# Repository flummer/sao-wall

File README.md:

# SAO Wall

This is a design for a large PCB (300x400mm) with 16 SAO connectors to work either as a standalone display (fits in an IKEA RÖDALM picture frame) or be monted along with other panels to form a larger wall for displaying many SAOs.

This is heavily inspired by [Brian Benchoffs SAO Wall](https://bbenchoff.github.io/pages/ShittyWall.html), that has been used at several Supercon events, but this design does a few things slightly different, not least the power setup.

## Main concept and idea

The design is separated into two parts:

- SAO Connector board, which is the large PCB, that has all the connectors, polyfuses for each output and then a set of connectors for hooking up to the 4 power rails, the 2 I2C busses and all the GPIO pins for all SAOs
- USB-C PD and Pico controll board is the smaller board that has the voltage regulators (4x AP63203WU-7 buck converters), USB-C PD controller (STUSB4531) and a footprint for a Raspberry Pi Pico (1 or 2).

The setup with two boards is done so that the more generic part (the connector PCB) that is also a bit on the expensive side can be ordered once and maybe a combined order for multiple people, and then the more opinionated element with the powering circuit and maybe a micro controller can be easier made in low volume (most simple is a piece of proto board and a simple 3.3v poser supply).

The USB-C PD power setup that is included here is meant to work nicely with most USB-C power supplies and at the same time be able to power all 16 SAOs to the full specification of the SAO standard (250mA @ 3.3V for each SAO).

The Raspberry Pi Pico is connected very similar to hos the [Hackaday SAO Badge](https://github.com/Hack-a-Day/2024-Supercon-8-Add-On-Badge) was made, with 2 I2C busses (using the same pins) and hooked up to GPIO pins of most of the SAOs (10 out of the 16) as there is a limited number of available connections on the Pico. It's not 100% pin compatible with the Hackaday SAO Badge, but it should be an easy tweak if you would like to run the same firmware.

## Designed in KiCad v10

To open the project, you will need to install the most recent release (v10), KiCad v9 or earlier won't open this design directly.

[Electronics schematics for the connector board as a PDF file](https://github.com/flummer/sao-wall/blob/main/sao-connector-board-schematics.pdf) and [Electronics schematics for the USB-C PD and Pico control board as a PDF file](https://github.com/flummer/sao-wall/blob/main/usb-pd-pico-controller-schematics.pdf) are included for reference.

## License

The hardware design of the `main` branch of this repository is released under the following license:

* the "Creative Commons Attribution-ShareAlike 4.0 International License"
  (CC BY-SA 4.0) full text of this license is included in the LICENSE file
  and a copy can also be found at
  [http://creativecommons.org/licenses/by-sa/4.0/](http://creativecommons.org/licenses/by-sa/4.0/)

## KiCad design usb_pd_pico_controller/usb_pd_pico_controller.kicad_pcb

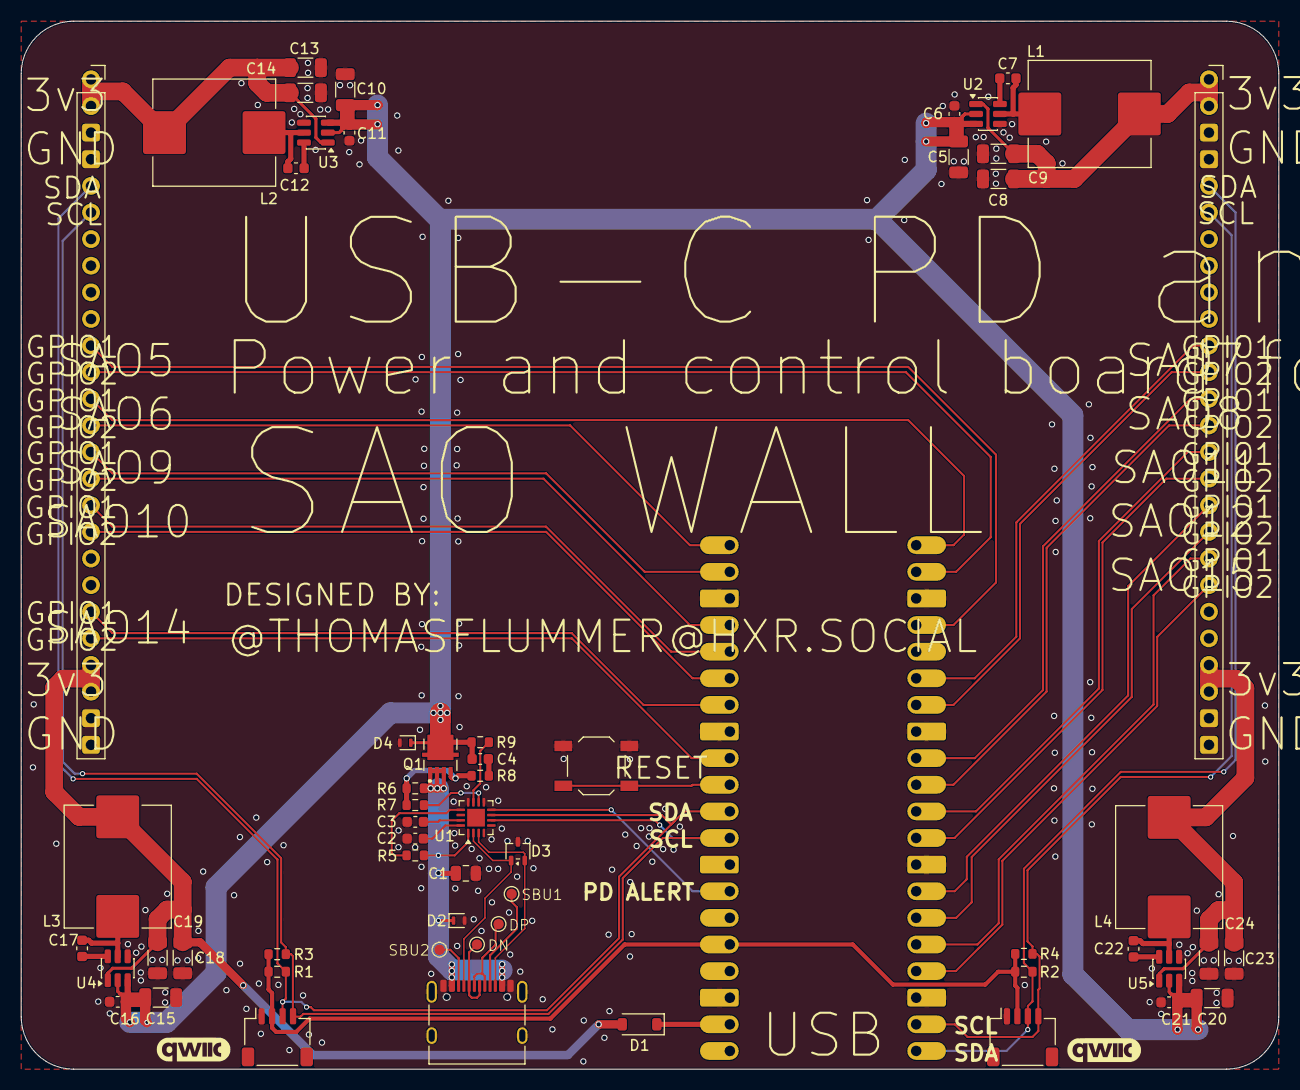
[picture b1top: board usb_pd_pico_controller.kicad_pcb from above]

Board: 2 copper layers, 120.0 x 100.0 mm, 59 parts (0 on the bottom side), 56 nets.

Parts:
C1: 4.7uF, 35V; C_0805_2012Metric
C2, C3: 1uF; C_0603_1608Metric
C4, C6, C7, C11, C12, C16, C17, C21, C22: 100nF, X5R/X7R, 50V; C_0603_1608Metric
C5, C10, C15, C20: 10uF, X5R/X7R, 35V; C_1206_3216Metric
C8, C9, C13, C14, C18, C19, C23, C24: 22uF, X5R/X7R, 25V; C_1206_3216Metric
D1: MBR120VLSFT1G; D_SOD-123
D2, D4: ESDA25P35-1U1M; ST_QFN-2L_1.6x1.0mm
D3: ESDA25W; SOT-323_SC-70
J1, J2: LCSC C145956; JST_SH_SM04B-SRSS-TB_1x04-1MP_P1.00mm_Horizontal
J3, J4: Conn_01x26_Socket; PinSocket_1x26_P2.54mm_Vertical
J5: USB_C_Receptacle_USB2.0_16P; USB_C_Receptacle_XKB_U262-16XN-4BVC11
J6, J7: Conn_01x20_Socket; PinSocket_1x20_P2.54mm_Vertical
L1, L2, L3, L4: 6.8uH; L_Sunlord_MWSA1005S
Q1: STL6P3LLH6; TRANS_STL6P3LLH6
R1, R2, R3, R4: 10K; R_0603_1608Metric
R5, R9: 1K; R_0603_1608Metric
R6: 100K; R_0603_1608Metric
R7: 22K; R_0603_1608Metric
R8: 100; R_0603_1608Metric
SW1: TS5220A; SW_SPST_TL3342
TP1, TP2, TP3, TP4: TestPoint; TestPoint_Pad_D1.0mm
U1: STUSB4531QTR; QFN-16-1EP_3x3mm_P0.5mm_EP1.7x1.7mm
U2, U3, U4, U5: AP63203WU; TSOT-23-6

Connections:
/PD Controller/CC1: D3.1 (K), J5.A5 (CC1), U1.2 (CC1)
/PD Controller/CC2: D3.2 (K), J5.B5 (CC2), U1.3 (CC2)
/PD Controller/D_N: J5.A7 (D-), J5.B7 (D-), TP2.1 (1_1)
/PD Controller/D_P: J5.A6 (D+), J5.B6 (D+), TP1.1 (1_1)
/PD Controller/SBU1: J5.A8 (SBU1), TP4.1 (1_1)
/PD Controller/SBU2: J5.B8 (SBU2), TP3.1 (1_1)
/PD Controller/VBUS: C1.1, D2.1 (K), J5.A4 (VBUS), J5.A9 (VBUS), J5.B4 (VBUS), J5.B9 (VBUS), Q1.1 (S1), Q1.2 (S1), Q1.3 (S1), R5.1, R6.1, U1.1 (VDD)
/RPi Pico X/RUN: J7.10, SW1.2 (B)
/RPi Pico X/VSYS: D1.1 (K), J7.19
/V_NEGOTIATED: C4.2, C5.1, C6.1, C10.1, C11.1, C15.1, C16.1, C20.1, C21.1, D4.1 (K), Q1.5_8 (D1), R9.1, U2.2 (EN), U2.3 (IN), U3.2 (EN), U3.3 (IN), U4.2 (EN), U4.3 (IN), U5.2 (EN), U5.3 (IN)
GND: C1.2, C2.2, C3.2, C5.2, C6.2, C8.2, C9.2, C10.2, C11.2, C13.2, C14.2, C15.2, C16.2, C18.2, C19.2, C20.2, C21.2, C23.2, C24.2, D2.2 (A), D3.3 (A), D4.2 (A), J1.1, J2.1, J3.3, J3.4, J3.25, J3.26, J4.3, J4.4, J4.25, J4.26, J5.A1 (GND), J5.A12 (GND), J5.B1 (GND), J5.B12 (GND), J5.SH (SHIELD), J6.3, J6.8, J6.13, J6.18, J7.3, J7.8, J7.18, SW1.1 (A), U1.9 (ADDR0), U1.12 (GND), U2.4 (GND), U3.4 (GND), U4.4 (GND), U5.4 (GND)
unnamed: C4.1, R8.1
unnamed: Q1.4 (G1), R6.2, R7.1, R8.2
unnamed: R9.2, U1.11 (DISCH)
unnamed: R7.2, U1.10 (VBUS_EN_SNK)
unnamed: R5.2, U1.13 (VBUS_VS_DISCH)
unnamed: C3.1, U1.15 (VREG_1V2)
unnamed: C2.1, U1.16 (VREG_2V7)
unnamed: C7.2, U2.6 (BST)
unnamed: C7.1, L1.1, U2.5 (SW)
unnamed: C12.2, U3.6 (BST)
unnamed: C12.1, L2.1, U3.5 (SW)
unnamed: C17.2, U4.6 (BST)
unnamed: C17.1, L3.1, U4.5 (SW)
unnamed: C22.2, U5.6 (BST)
unnamed: C22.1, L4.1, U5.5 (SW)
PD_ALERT: J7.14, U1.8 (ALERT)
SAO5_GPIO1: J3.11, J6.17
SAO5_GPIO2: J3.12, J6.19
SAO6_GPIO1: J3.13, J6.20
SAO6_GPIO2: J3.14, J7.1
SAO7_GPIO1: J4.11, J6.15
SAO7_GPIO2: J4.12, J6.14
SAO8_GPIO1: J4.13, J6.12
SAO8_GPIO2: J4.14, J6.11
SAO9_GPIO1: J3.15, J7.2
SAO9_GPIO2: J3.16, J7.4
SAO10_GPIO1: J3.17, J7.5
SAO10_GPIO2: J3.18, J7.6
SAO11_GPIO1: J4.15, J6.10
SAO11_GPIO2: J4.16, J6.9
SAO12_GPIO1: J4.17, J6.7
SAO12_GPIO2: J4.18, J6.6
SAO14_GPIO1: J3.21, J7.7
SAO14_GPIO2: J3.22, J7.9
SAO15_GPIO1: J4.19, J6.5
SAO15_GPIO2: J4.20, J6.4
SCL_LEFT: J1.4, J3.6, J7.12, R3.2, U1.6 (SCL)
SCL_RIGHT: J2.4, J4.6, J6.2, R4.2
SDA_LEFT: J1.3, J3.5, J7.11, R1.2, U1.7 (SDA)
SDA_RIGHT: J2.3, J4.5, J6.1, R2.2
VCC_PICO: J1.2, J2.2, J7.16, R1.1, R2.1, R3.1, R4.1
VCC_Q1: C8.1, C9.1, J4.1, J4.2, L1.2, U2.1 (FB)
VCC_Q2: C13.1, C14.1, J3.1, J3.2, L2.2, U3.1 (FB)
VCC_Q3: C18.1, C19.1, D1.2 (A), J3.23, J3.24, L3.2, U4.1 (FB)
VCC_Q4: C23.1, C24.1, J4.23, J4.24, L4.2, U5.1 (FB)

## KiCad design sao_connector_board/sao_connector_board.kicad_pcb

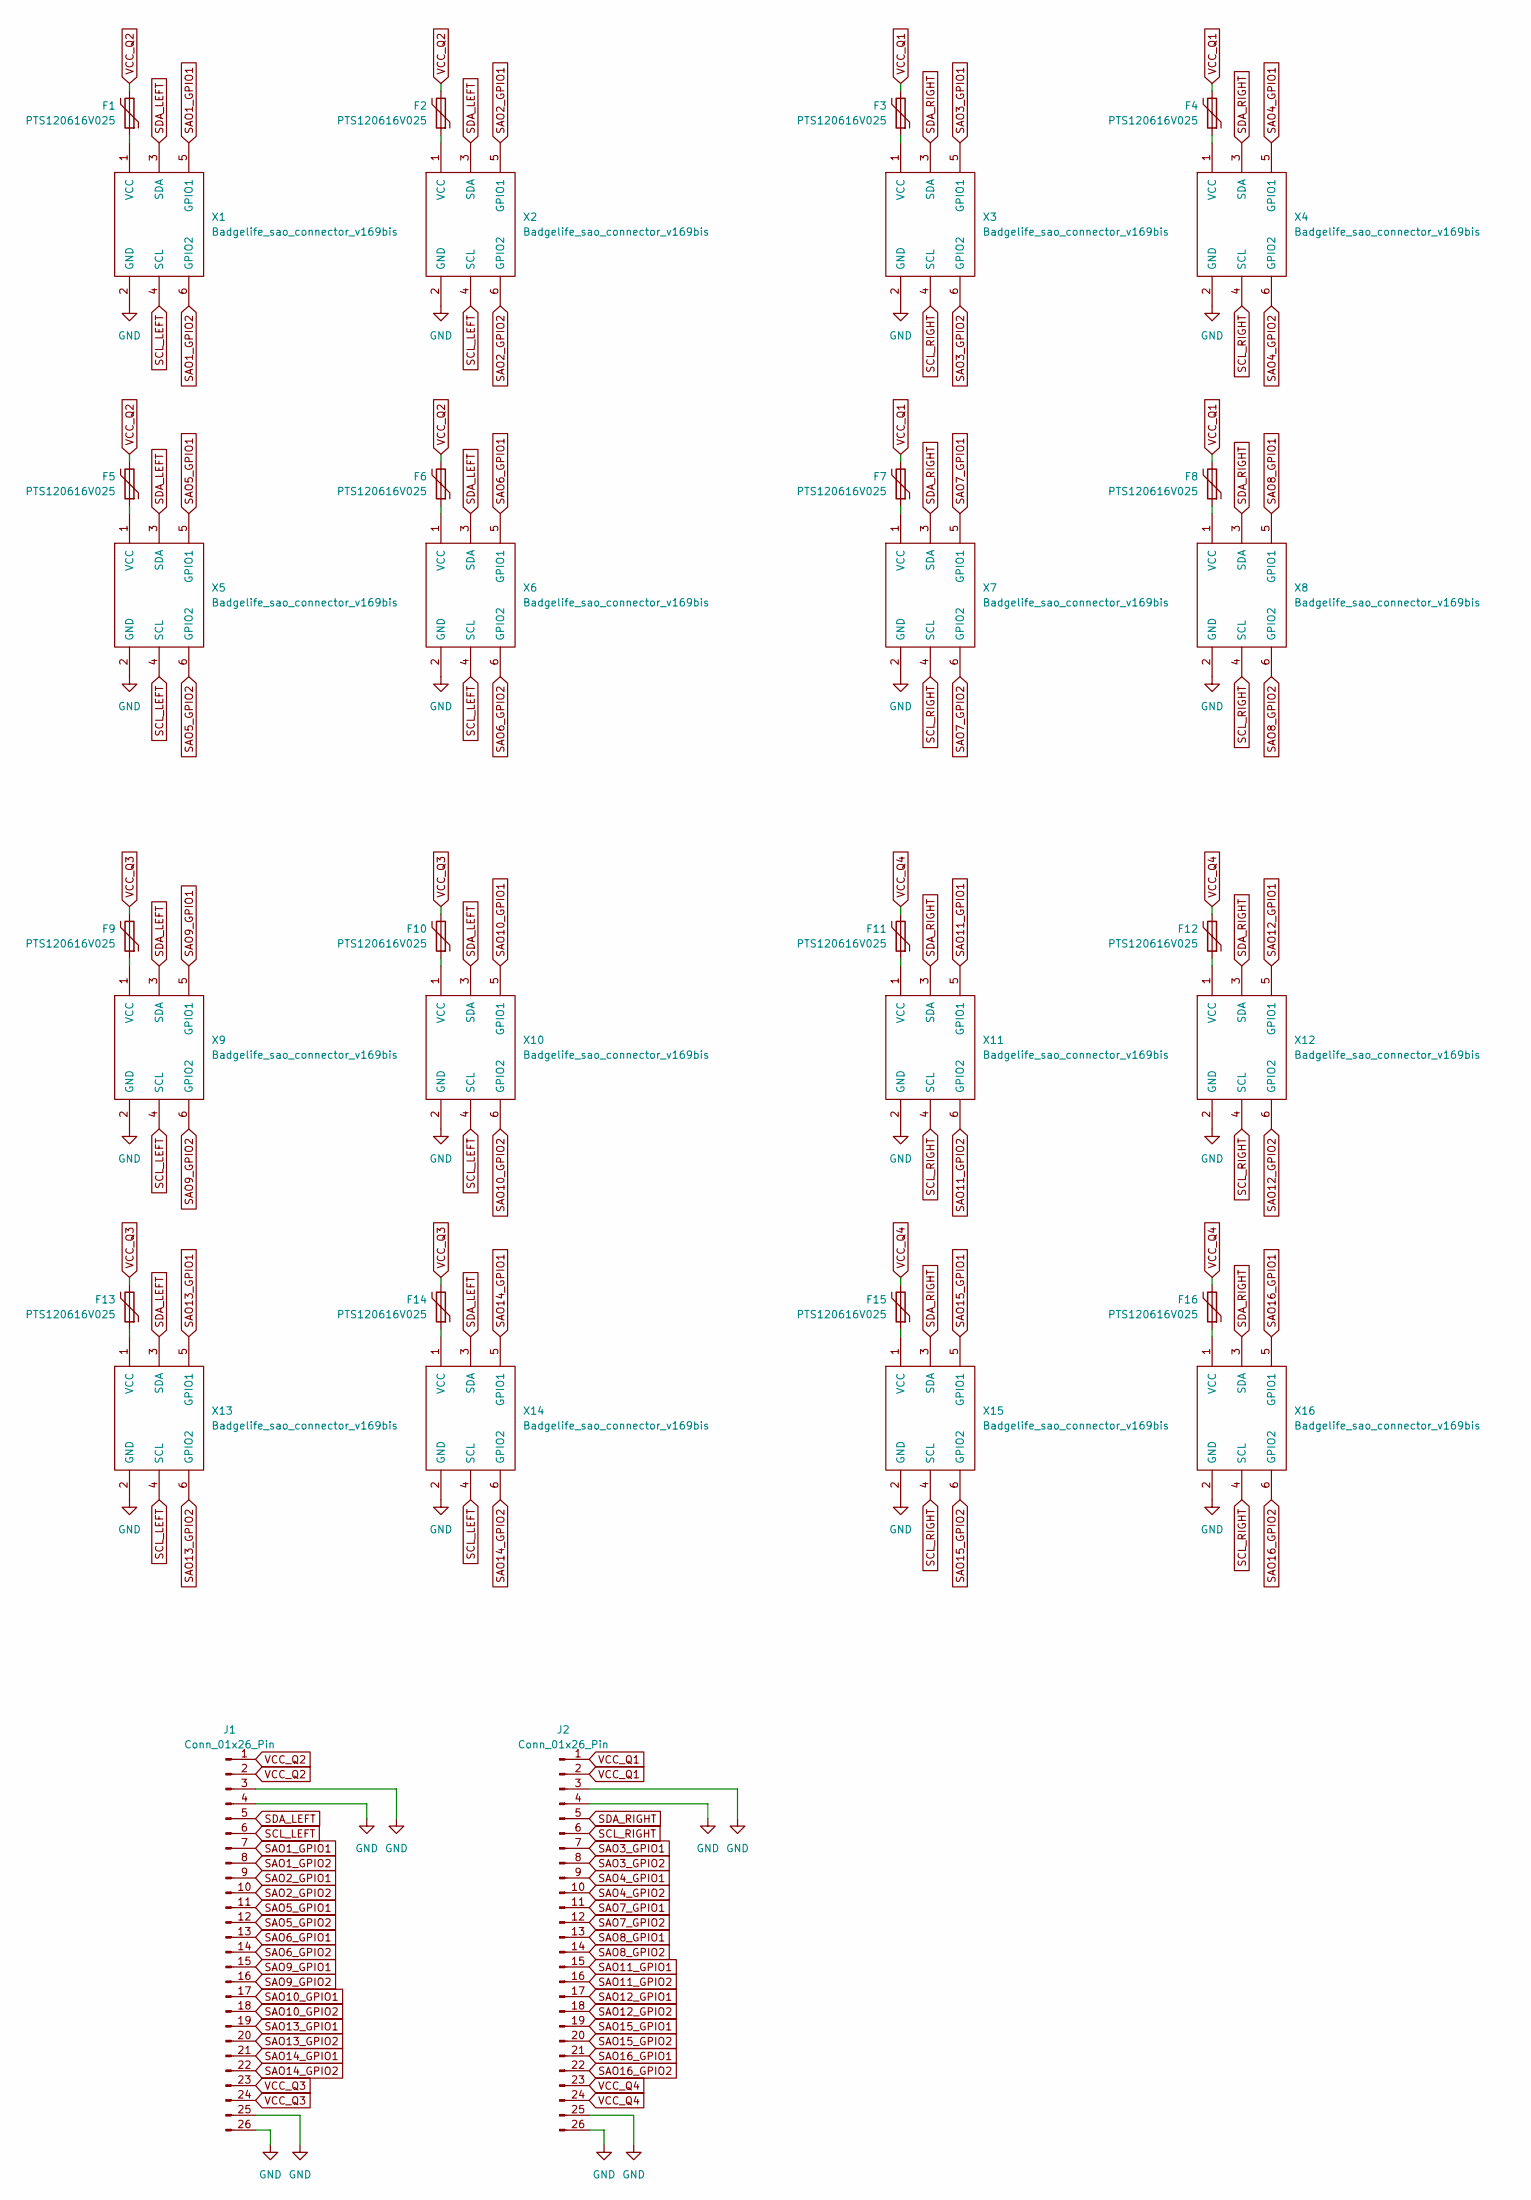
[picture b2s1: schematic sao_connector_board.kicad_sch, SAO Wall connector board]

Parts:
F1, F2, F3, F4, F5, F6, F7, F8, F9, F10, F11, F12, F13, F14, F15, F16: PTS120616V025; Fuse_1206_3216Metric_Pad1.42x1.75mm_HandSolder
J1, J2: Conn_01x26_Pin; PinHeader_1x26_P2.54mm_Vertical_SMD_Pin1Left
X1, X2, X3, X4, X5, X6, X7, X8, X9, X10, X11, X12, X13, X14, X15, X16: Badgelife_sao_connector_v169bis; Badgelife-SAOv169-BADGE-2x3-clean-front

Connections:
GND: J1.3, J1.4, J1.25, J1.26, J2.3, J2.4, J2.25, J2.26, X1.2 (GND), X2.2 (GND), X3.2 (GND), X4.2 (GND), X5.2 (GND), X6.2 (GND), X7.2 (GND), X8.2 (GND), X9.2 (GND), X10.2 (GND), X11.2 (GND), X12.2 (GND), X13.2 (GND), X14.2 (GND), X15.2 (GND), X16.2 (GND)
unnamed: F1.1, X1.1 (VCC)
unnamed: F2.1, X2.1 (VCC)
unnamed: F3.1, X3.1 (VCC)
unnamed: F4.1, X4.1 (VCC)
unnamed: F5.1, X5.1 (VCC)
unnamed: F6.1, X6.1 (VCC)
unnamed: F7.1, X7.1 (VCC)
unnamed: F8.1, X8.1 (VCC)
unnamed: F9.1, X9.1 (VCC)
unnamed: F10.1, X10.1 (VCC)
unnamed: F11.1, X11.1 (VCC)
unnamed: F12.1, X12.1 (VCC)
unnamed: F13.1, X13.1 (VCC)
unnamed: F14.1, X14.1 (VCC)
unnamed: F15.1, X15.1 (VCC)
unnamed: F16.1, X16.1 (VCC)
SAO1_GPIO1: J1.7, X1.5 (GPIO1)
SAO1_GPIO2: J1.8, X1.6 (GPIO2)
SAO2_GPIO1: J1.9, X2.5 (GPIO1)
SAO2_GPIO2: J1.10, X2.6 (GPIO2)
SAO3_GPIO1: J2.7, X3.5 (GPIO1)
SAO3_GPIO2: J2.8, X3.6 (GPIO2)
SAO4_GPIO1: J2.9, X4.5 (GPIO1)
SAO4_GPIO2: J2.10, X4.6 (GPIO2)
SAO5_GPIO1: J1.11, X5.5 (GPIO1)
SAO5_GPIO2: J1.12, X5.6 (GPIO2)
SAO6_GPIO1: J1.13, X6.5 (GPIO1)
SAO6_GPIO2: J1.14, X6.6 (GPIO2)
SAO7_GPIO1: J2.11, X7.5 (GPIO1)
SAO7_GPIO2: J2.12, X7.6 (GPIO2)
SAO8_GPIO1: J2.13, X8.5 (GPIO1)
SAO8_GPIO2: J2.14, X8.6 (GPIO2)
SAO9_GPIO1: J1.15, X9.5 (GPIO1)
SAO9_GPIO2: J1.16, X9.6 (GPIO2)
SAO10_GPIO1: J1.17, X10.5 (GPIO1)
SAO10_GPIO2: J1.18, X10.6 (GPIO2)
SAO11_GPIO1: J2.15, X11.5 (GPIO1)
SAO11_GPIO2: J2.16, X11.6 (GPIO2)
SAO12_GPIO1: J2.17, X12.5 (GPIO1)
SAO12_GPIO2: J2.18, X12.6 (GPIO2)
SAO13_GPIO1: J1.19, X13.5 (GPIO1)
SAO13_GPIO2: J1.20, X13.6 (GPIO2)
SAO14_GPIO1: J1.21, X14.5 (GPIO1)
SAO14_GPIO2: J1.22, X14.6 (GPIO2)
SAO15_GPIO1: J2.19, X15.5 (GPIO1)
SAO15_GPIO2: J2.20, X15.6 (GPIO2)
SAO16_GPIO1: J2.21, X16.5 (GPIO1)
SAO16_GPIO2: J2.22, X16.6 (GPIO2)
SCL_LEFT: J1.6, X1.4 (SCL), X2.4 (SCL), X5.4 (SCL), X6.4 (SCL), X9.4 (SCL), X10.4 (SCL), X13.4 (SCL), X14.4 (SCL)
SCL_RIGHT: J2.6, X3.4 (SCL), X4.4 (SCL), X7.4 (SCL), X8.4 (SCL), X11.4 (SCL), X12.4 (SCL), X15.4 (SCL), X16.4 (SCL)
SDA_LEFT: J1.5, X1.3 (SDA), X2.3 (SDA), X5.3 (SDA), X6.3 (SDA), X9.3 (SDA), X10.3 (SDA), X13.3 (SDA), X14.3 (SDA)
SDA_RIGHT: J2.5, X3.3 (SDA), X4.3 (SDA), X7.3 (SDA), X8.3 (SDA), X11.3 (SDA), X12.3 (SDA), X15.3 (SDA), X16.3 (SDA)
VCC_Q1: F3.2, F4.2, F7.2, F8.2, J2.1, J2.2
VCC_Q2: F1.2, F2.2, F5.2, F6.2, J1.1, J1.2
VCC_Q3: F9.2, F10.2, F13.2, F14.2, J1.23, J1.24
VCC_Q4: F11.2, F12.2, F15.2, F16.2, J2.23, J2.24

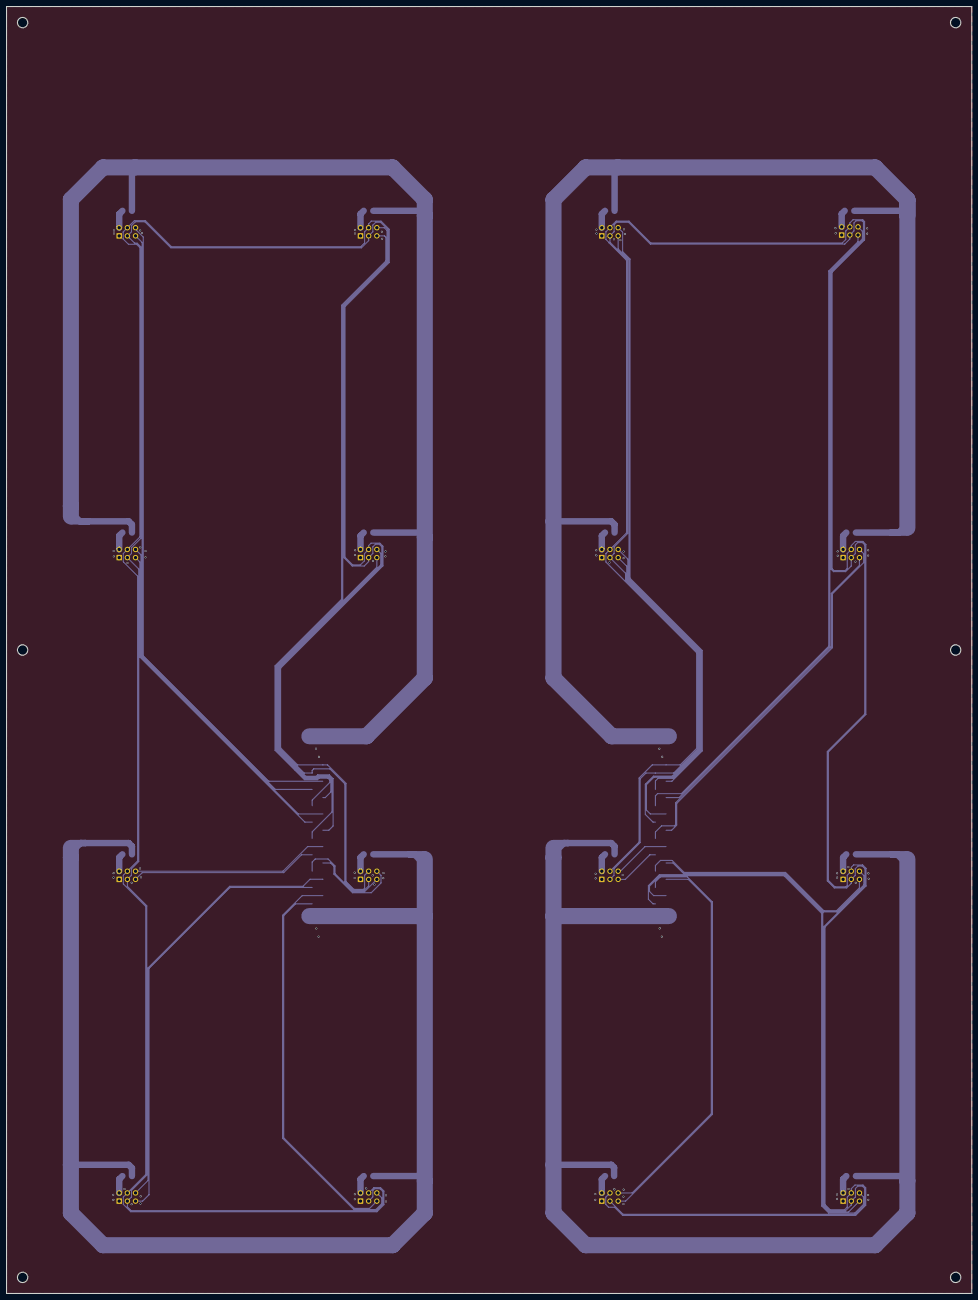
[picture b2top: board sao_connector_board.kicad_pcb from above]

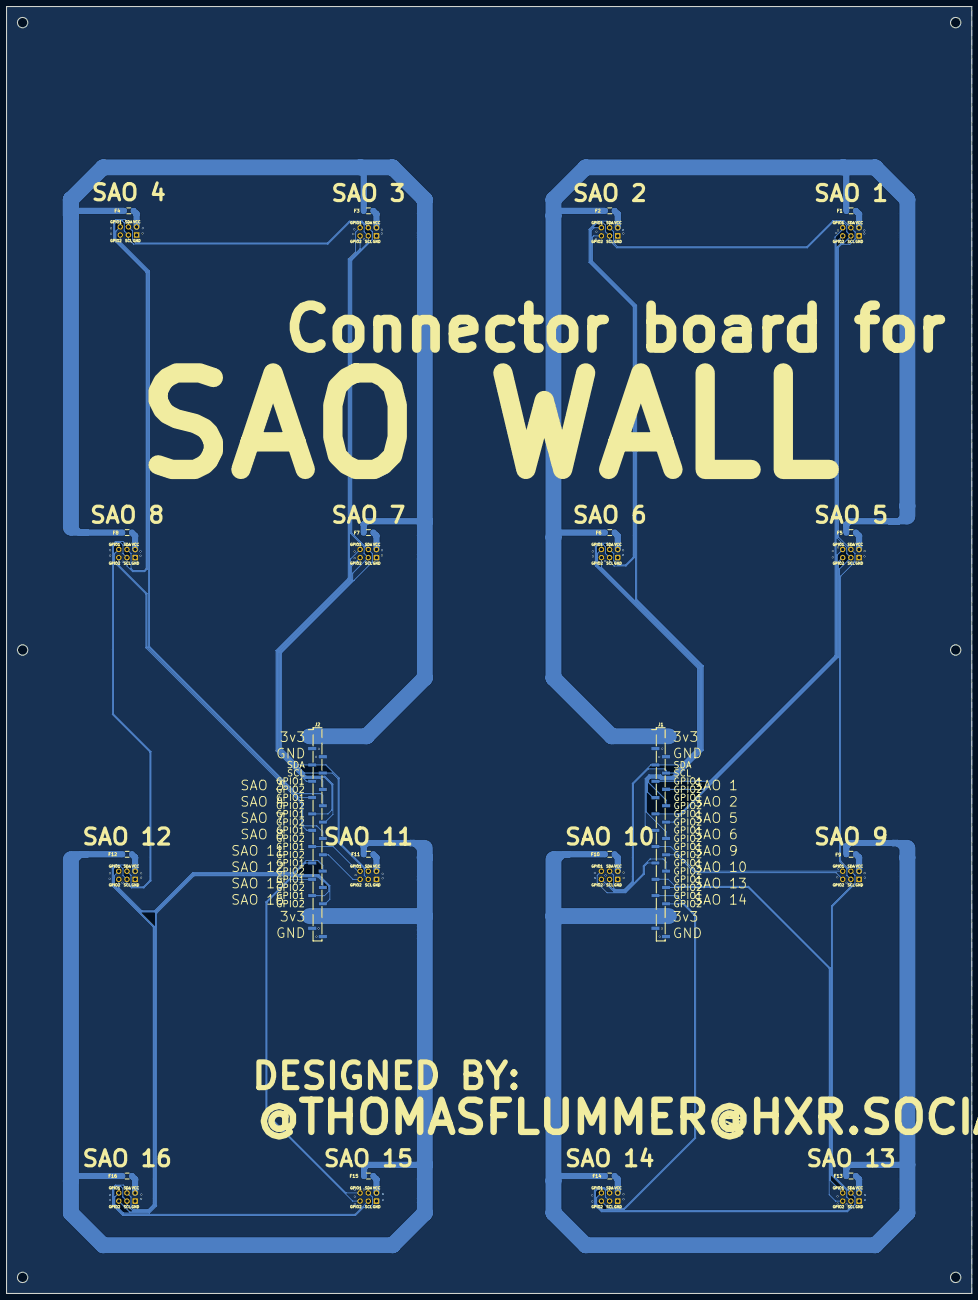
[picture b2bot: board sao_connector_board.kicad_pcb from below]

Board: 2 copper layers, 300.0 x 400.0 mm, 34 parts (18 on the bottom side), 57 nets.

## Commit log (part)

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2026-04-27 Added missing link to SAO badge
